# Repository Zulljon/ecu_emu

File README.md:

# ECU emulator v3.1a
PCB part of project (source codes unavailable!)

## Scheme

## PCB

### With FreeCAD PCB mod

### With FreeCAD KiCAD StepUp mod

## Tools
- KiCAD v4.0.7
- FreeCAD v0.15

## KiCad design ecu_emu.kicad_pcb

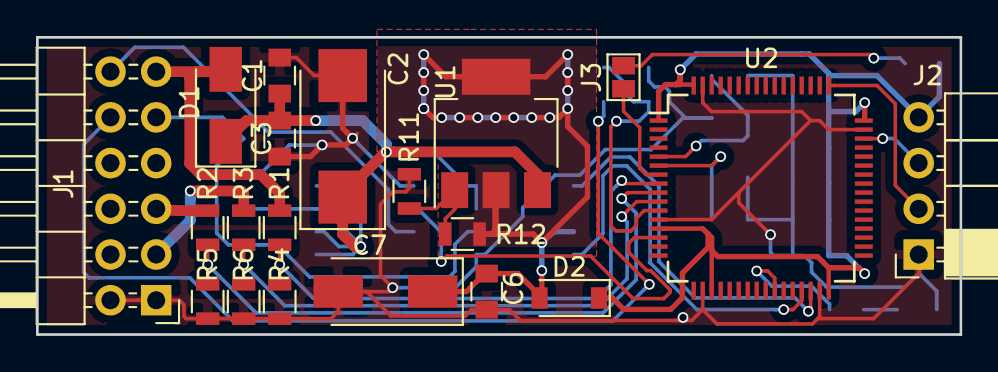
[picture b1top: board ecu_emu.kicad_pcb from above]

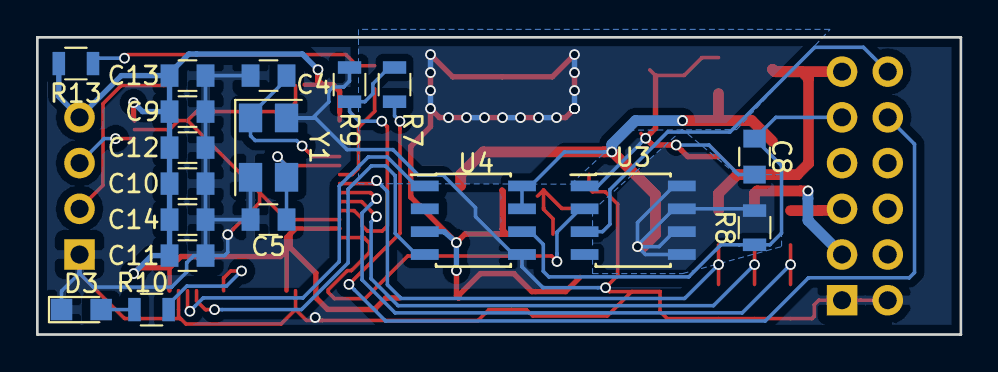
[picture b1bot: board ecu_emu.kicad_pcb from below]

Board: 2 copper layers, 51.3 x 16.5 mm, 38 parts (18 on the bottom side), 26 nets.

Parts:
C1: 10nF; C_0805
C2: 220uF x 30V; CP_Tantalum_Case-X_EIA-7343-43_Wave
C3, C10, C11, C12, C13, C14: 100nF; C_0805
C4, C5: 16pF; C_0805
C6: 10uF; C_0805
C7: 47uF x 16V; CP_Tantalum_Case-C_EIA-6032-28_Wave
C8: 1nF; C_0805
C9: 4.7uF; C_0805
D1: SS22A-SS210A-Galaxy; D_SMA
D2: 1N5819HW-7-F; D_SOD-123
D3: LED; LED_0805
J1: Conn_02x06_Odd_Even; Pin_Header_Angled_2x06_Pitch2.54mm
J2: Conn_01x04_Male; Socket_Strip_Angled_1x04_Pitch2.54mm
J3: GS2
R1, R2, R3: 9k; R_0805
R4, R5, R6: 2k2; R_0805
R7, R8, R9, R10: 1k; R_0805
R11: 240; R_0805
R12: 120; R_0805
R13: 100k; R_0805
U1: AMS1117-ADJ; SOT-223-3_TabPin2
U2: STM32F105RBTx; LQFP-64_10x10mm_Pitch0.5mm
U3: BSP742R; SOIC-8_3.9x4.9mm_Pitch1.27mm
U4: E-L9637D; SOIC-8_3.9x4.9mm_Pitch1.27mm
Y1: Crystal KX-9A; Crystal_SMD_5032-4pin_5.0x3.2mm

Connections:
/+3V3: C6.1, C7.1, D2.2, R12.1, U1.2, U4.3
/+3V3_STM: C9.1, C10.1, C11.1, C12.1, C13.1, C14.1, D2.1, J2.4, R13.2, U2.1, U2.13, U2.19, U2.32, U2.48, U2.64
/ADC_AUX: R3.1, R6.2, U2.10
/ADC_IGN: R2.1, R5.2, U2.9
/ADC_Vbatt: R1.1, R4.2, U2.8
/ECU_AUX: J1.3, R3.2
/ECU_HALL_sensor+: J1.10, R7.2
/ECU_IGN: J1.5, R2.2
/ECU_Kbus: C8.1, J1.9, R8.1, U4.6
/ECU_Vbatt: D1.2, J1.11, R1.2
/ECU_solenoid: J1.12, U3.3
/Kbus_Vbatt: C1.1, C2.1, C3.1, D1.1, R8.2, U1.3, U3.5, U3.6, U3.7, U3.8, U4.7, U4.8
/NRST: J3.1, U2.7
/solenoid_driver: U2.14, U3.2
/stm2Kbus_UART_RX: U2.30, U4.1
/stm2Kbus_UART_TX: U2.29, U4.4
GND: C1.2, C2.2, C3.2, C4.2, C5.2, C6.2, C7.2, C8.2, C9.2, C10.2, C11.2, C12.2, C13.2, C14.2, D3.1, J1.1, J1.2, J2.1, R4.1, R5.1, R6.1, R9.1, R11.2, U2.12, U2.18, U2.31, U2.47, U2.63, U3.1, U4.5, Y1.2, Y1.4
unnamed: C4.1, U2.5, Y1.1
unnamed: C5.1, U2.6, Y1.3
unnamed: D3.2, R10.1
unnamed: J2.2, U2.49
unnamed: J2.3, U2.46
unnamed: J3.2, R13.1
unnamed: R7.1, R9.2, U2.11
unnamed: R10.2, U2.26
unnamed: R11.1, R12.2, U1.1

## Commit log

2017-10-26 init local repo
2017-10-26 add README file, with svg graphics
2017-11-03 refresh image according to new changes
2017-11-03 1. solenoid rules with MOSFET and his driver 2. chane LIN to K-Bus cirquit 3. add shotky diod
2017-11-04 add 3D wiev of pcb
2017-11-05 add second 3d modele
2017-11-06 sch: add resistor to hall sensor input
2017-11-06 add NET file
2017-11-06 add drawing of pcb
2017-11-06 add graphics to git readme file
2017-11-15 switch to my library https://github.com/Zulljon/zpkl.git
2017-12-02 scheme: change solenoid driver, add capasitors to stm power supply, fix crystal package
2017-12-02 pcb: swd conn to socket strip, applied sch changes from 059fb19
2017-12-04 pcb: add additional vias and zones to linear stabilazer on bottom side
2017-12-05 sch&pcb: add one LED and refresh readme image
2017-12-06 generate gerber files & add .sh to zip them
2017-12-06 zipped gerber files
2017-12-08 add descriptions for gerber files
2017-12-08 refresh images
2017-12-08 add BOM file
2018-01-16 fix libs path
2018-01-26 more fixes 1. separate power on k-bus IC logic 2. D2 change to shottky diod 3. pull-up on stm RESET pin 4. change linier stabilizer to adjastable version, to make apropriate voltage on stm throw diod
2019-01-18 improve zip script
2019-01-18 fix some, update gerbers
2019-01-18 fix chmod a-x
